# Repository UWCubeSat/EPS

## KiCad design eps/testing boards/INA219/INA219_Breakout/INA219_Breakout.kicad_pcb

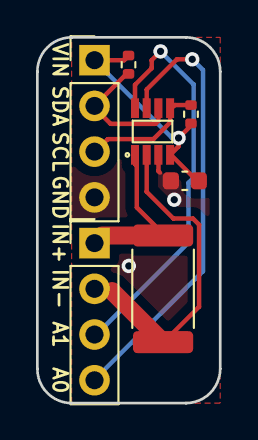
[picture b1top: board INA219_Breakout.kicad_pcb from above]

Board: 2 copper layers, 10.2 x 20.3 mm, 7 parts (0 on the bottom side), 8 nets.

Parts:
C1: C_Small; C_0603_1608Metric
J1, J2: Conn_01x04_Male; PinHeader_1x04_P2.54mm_Vertical
R1: Shunt; R_2512_6332Metric
R2, R3: 10K; R_0402_1005Metric
U1: INA219B; SOT-23-8

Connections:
/A0: J2.4, U1.7
/A1: J2.3, U1.8
/GND: C1.2, J1.4, U1.3
/IN+: J2.1, R1.1, U1.1
/IN-: J2.2, R1.2, U1.2
/SCL: J1.3, R3.2, U1.5
/SDA: J1.2, R2.2, U1.6
/VIN: C1.1, J1.1, R2.1, R3.1, U1.4
